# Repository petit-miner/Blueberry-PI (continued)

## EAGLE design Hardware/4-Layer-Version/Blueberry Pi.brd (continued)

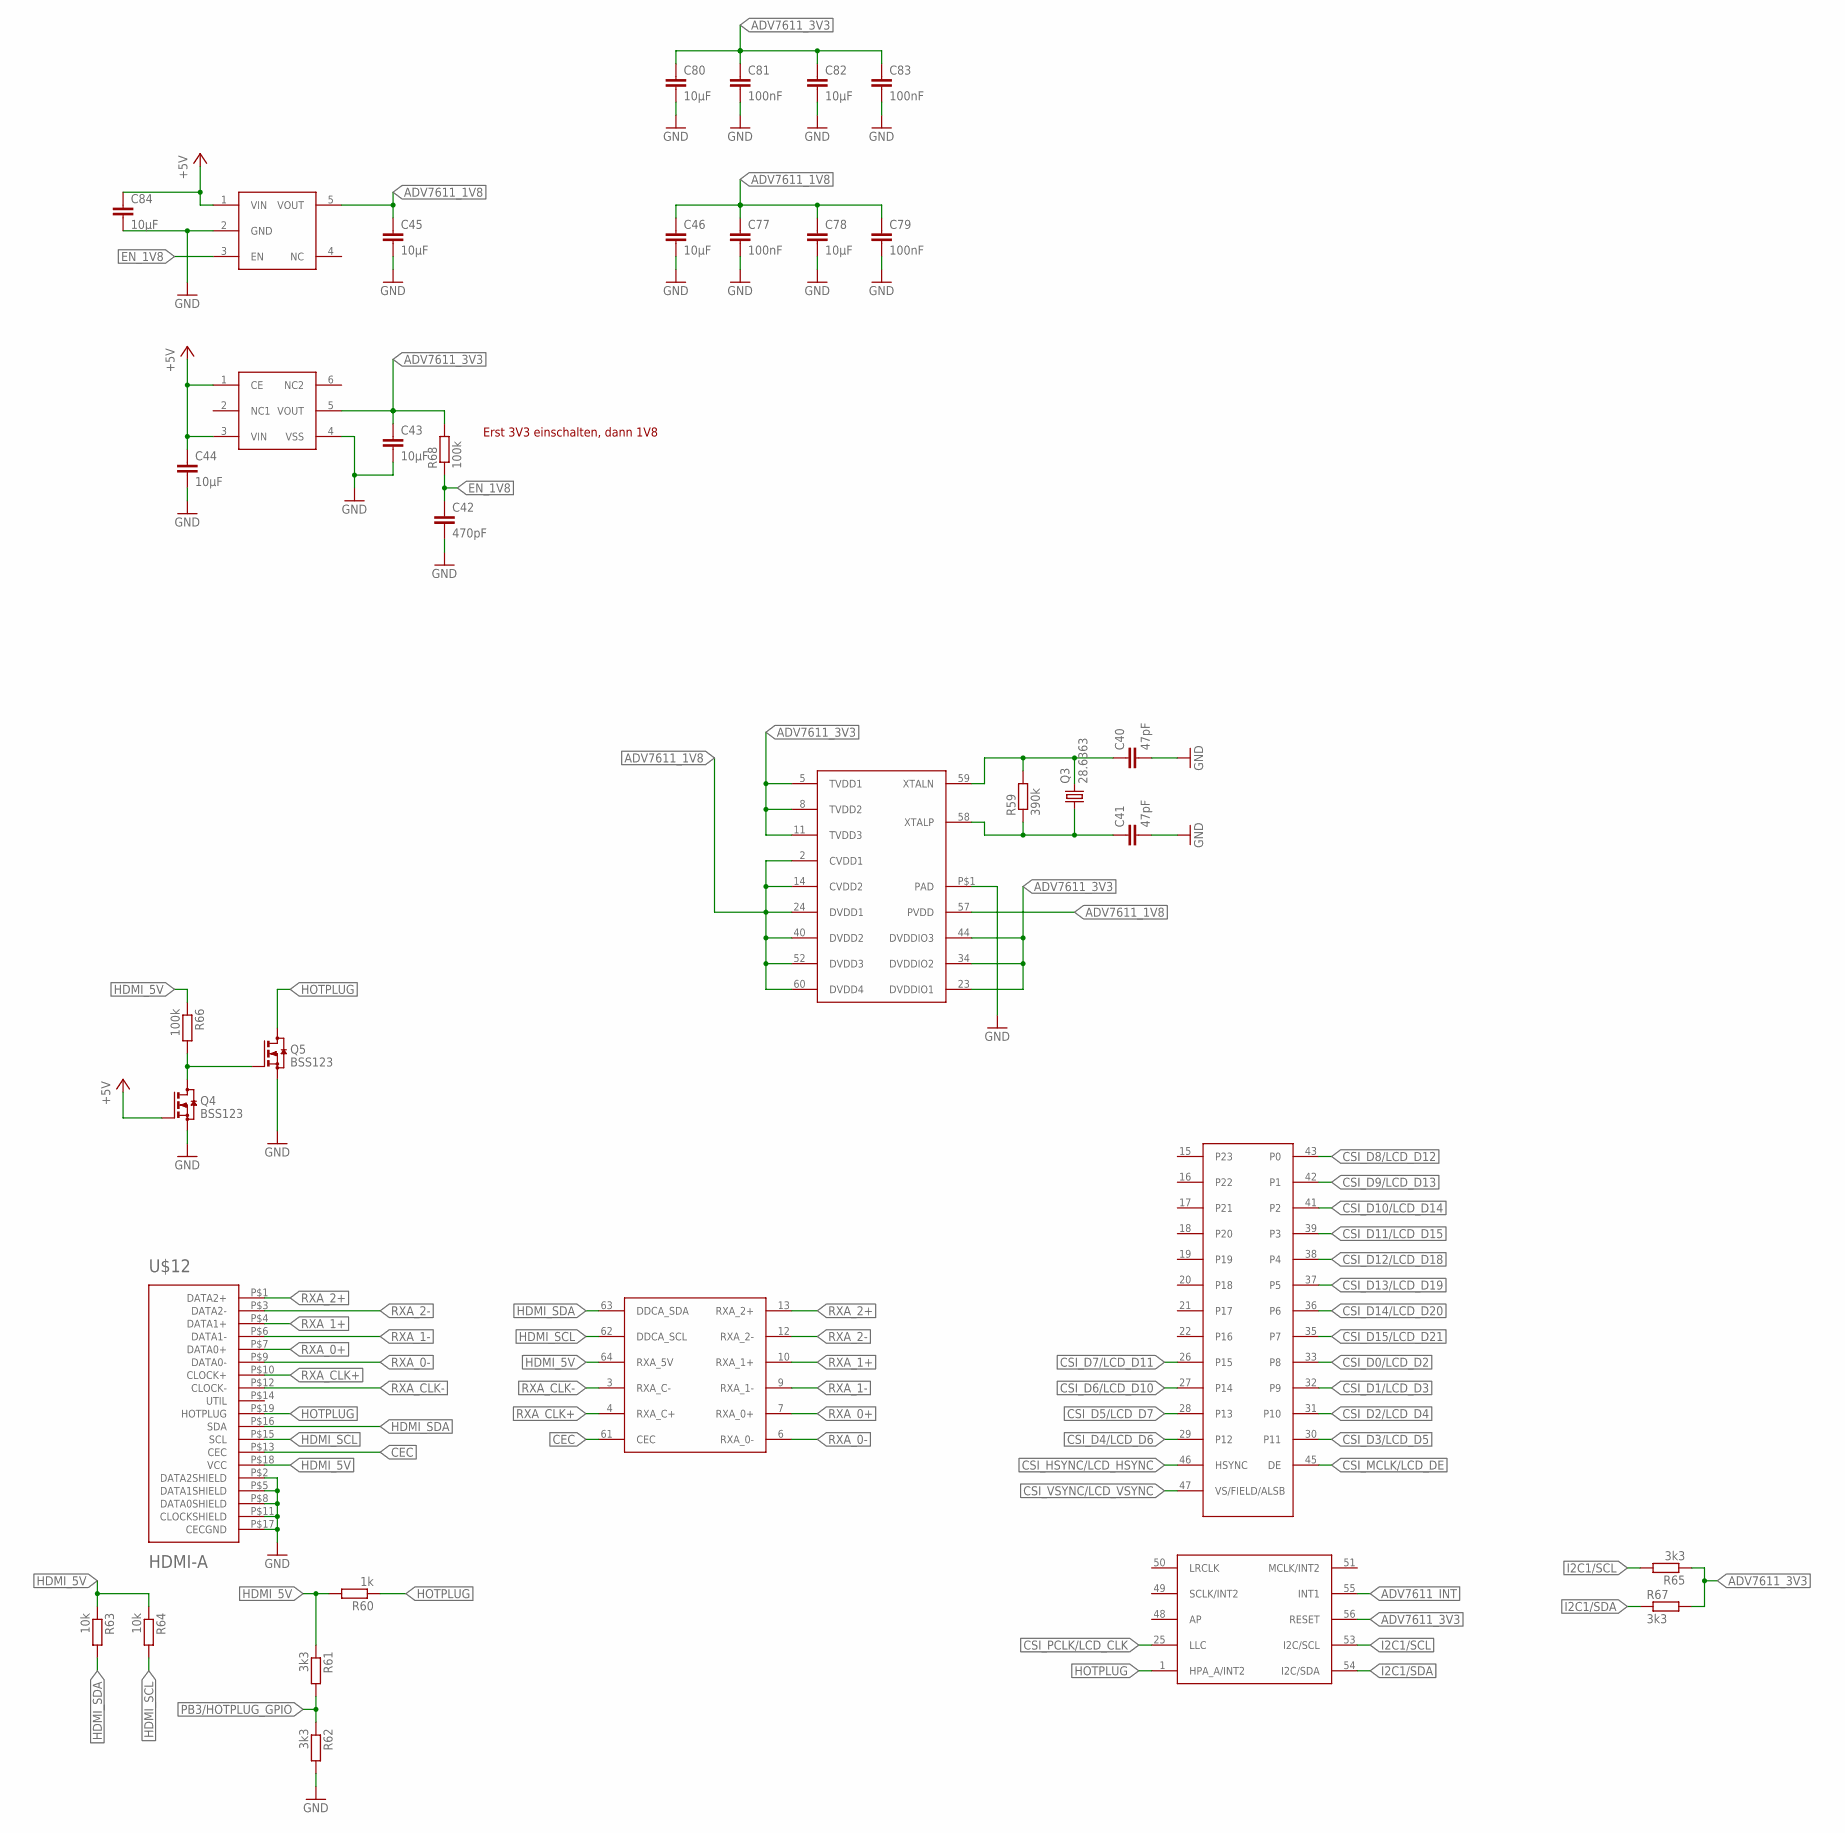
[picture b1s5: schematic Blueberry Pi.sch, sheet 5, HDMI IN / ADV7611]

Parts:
C40, C41: 47pF; C0603
C42: 470pF; C0603
C43, C44, C45, C46, C78, C80, C82, C84: 10µF; C0805
C77, C79, C81, C83: 100nF; C0603
Q3: 28.6363; HC49/S
Q4, Q5: BSS123; SOT23
R59: 390k; R0603
R60: 1k; R0603
R61, R62, R65, R67: 3k3; R0603
R63, R64: 10k; R0603
R66, R68: 100k; R0603
U$5: ADV7611; QFP50P1210X1210X120-65T500
U$12: HDMI-A; HDMI_A
U$13: XC6210B332MR-G; SOT-25
U$14: RT9013-18GB; SOT-23-5

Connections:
+5V: C44.1, C84.1, Q4.1 (G), U$13.1 (CE), U$13.3 (VIN), U$14.1 (VIN); also elsewhere on the board
ADV7611_1V8: C45.1, C46.1, C77.1, C78.1, C79.1, U$5.2 (CVDD1), U$5.14 (CVDD2), U$5.24 (DVDD1), U$5.40 (DVDD2), U$5.52 (DVDD3), U$5.57 (PVDD), U$5.60 (DVDD4), U$14.5 (VOUT)
ADV7611_3V3: C43.1, C80.1, C81.1, C82.1, C83.1, R65.1, R67.2, R68.2, U$5.5 (TVDD1), U$5.8 (TVDD2), U$5.11 (TVDD3), U$5.23 (DVDDIO1), U$5.34 (DVDDIO2), U$5.44 (DVDDIO3), U$5.56 (RESET), U$13.5 (VOUT)
ADV7611_INT: U$5.55 (INT1)
CEC: U$5.61 (CEC), U$12.P$13 (CEC)
CSI_D0/LCD_D2: U$5.33 (P8); also elsewhere on the board
CSI_D1/LCD_D3: U$5.32 (P9); also elsewhere on the board
CSI_D2/LCD_D4: U$5.31 (P10); also elsewhere on the board
CSI_D3/LCD_D5: U$5.30 (P11); also elsewhere on the board
CSI_D4/LCD_D6: U$5.29 (P12); also elsewhere on the board
CSI_D5/LCD_D7: U$5.28 (P13); also elsewhere on the board
CSI_D6/LCD_D10: U$5.27 (P14); also elsewhere on the board
CSI_D7/LCD_D11: U$5.26 (P15); also elsewhere on the board
CSI_D8/LCD_D12: U$5.43 (P0); also elsewhere on the board
CSI_D9/LCD_D13: U$5.42 (P1); also elsewhere on the board
CSI_D10/LCD_D14: U$5.41 (P2); also elsewhere on the board
CSI_D11/LCD_D15: U$5.39 (P3); also elsewhere on the board
CSI_D12/LCD_D18: U$5.38 (P4); also elsewhere on the board
CSI_D13/LCD_D19: U$5.37 (P5); also elsewhere on the board
CSI_D14/LCD_D20: U$5.36 (P6); also elsewhere on the board
CSI_D15/LCD_D21: U$5.35 (P7); also elsewhere on the board
CSI_HSYNC/LCD_HSYNC: U$5.46 (HSYNC); also elsewhere on the board
CSI_MCLK/LCD_DE: U$5.45 (DE); also elsewhere on the board
CSI_PCLK/LCD_CLK: U$5.25 (LLC); also elsewhere on the board
CSI_VSYNC/LCD_VSYNC: U$5.47 (VS/FIELD/ALSB); also elsewhere on the board
EN_1V8: C42.1, R68.1, U$14.3 (EN)
GND: C40.2, C41.2, C42.2, C43.2, C44.2, C45.2, C46.2, C77.2, C78.2, C79.2, C80.2, C81.2, C82.2, C83.2, C84.2, Q4.2 (S), Q5.2 (S), R62.2, U$5.P$1 (PAD), U$12.P$2 (DATA2SHIELD), U$12.P$5 (DATA1SHIELD), U$12.P$8 (DATA0SHIELD), U$12.P$11 (CLOCKSHIELD), U$12.P$17 (CECGND), U$13.4 (VSS), U$14.2 (GND); also elsewhere on the board
HDMI_5V: R60.2, R61.1, R63.1, R64.1, R66.1, U$5.64 (RXA_5V), U$12.P$18 (VCC)
HDMI_SCL: R64.2, U$5.62 (DDCA_SCL), U$12.P$15 (SCL)
HDMI_SDA: R63.2, U$5.63 (DDCA_SDA), U$12.P$16 (SDA)
HOTPLUG: Q5.3 (D), R60.1, U$5.1 (HPA_A/INT2), U$12.P$19 (HOTPLUG)
I2C1/SCL: R65.2, U$5.53 (I2C/SCL); also elsewhere on the board
I2C1/SDA: R67.1, U$5.54 (I2C/SDA); also elsewhere on the board
unnamed: C40.1, Q3.2, R59.2, U$5.59 (XTALN)
unnamed: C41.1, Q3.1, R59.1, U$5.58 (XTALP)
unnamed: Q4.3 (D), Q5.1 (G), R66.2
PB3/HOTPLUG_GPIO: R61.2, R62.1; also elsewhere on the board
RXA_0+: U$5.7 (RXA_0+), U$12.P$7 (DATA0+)
RXA_0-: U$5.6 (RXA_0-), U$12.P$9 (DATA0-)
RXA_1+: U$5.10 (RXA_1+), U$12.P$4 (DATA1+)
RXA_1-: U$5.9 (RXA_1-), U$12.P$6 (DATA1-)
RXA_2+: U$5.13 (RXA_2+), U$12.P$1 (DATA2+)
RXA_2-: U$5.12 (RXA_2-), U$12.P$3 (DATA2-)
RXA_CLK+: U$5.4 (RXA_C+), U$12.P$10 (CLOCK+)
RXA_CLK-: U$5.3 (RXA_C-), U$12.P$12 (CLOCK-)

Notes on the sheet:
Erst 3V3 einschalten, dann 1V8

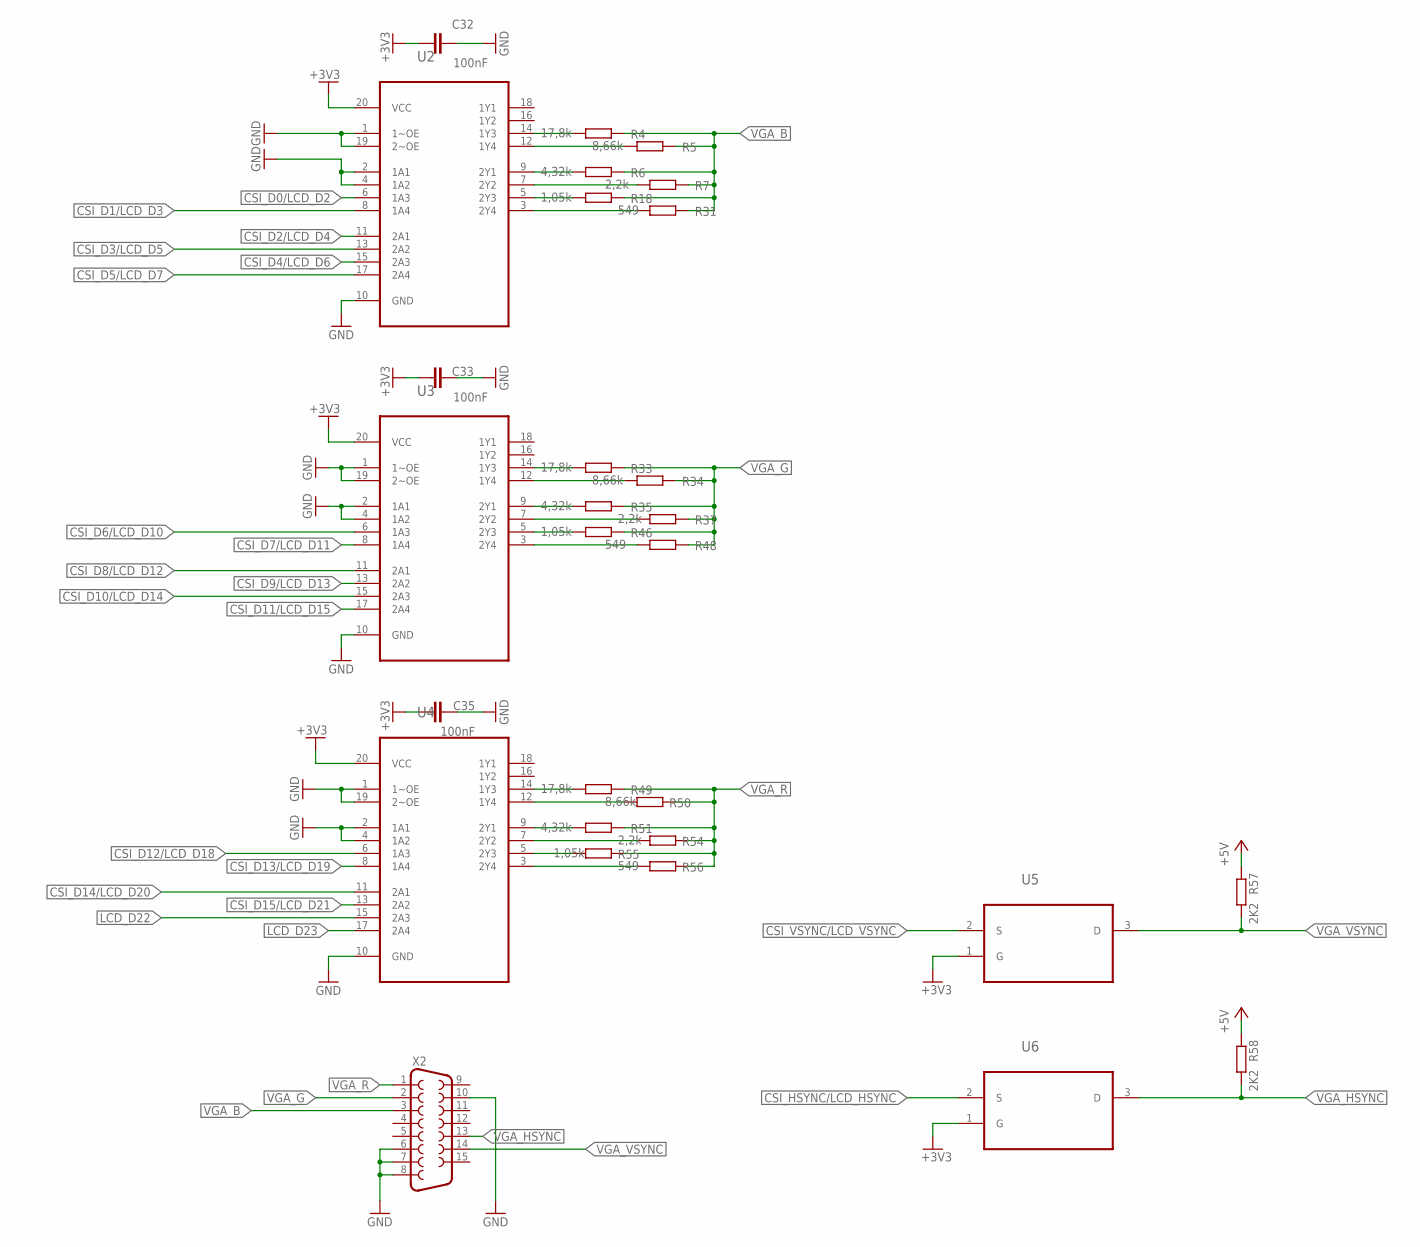
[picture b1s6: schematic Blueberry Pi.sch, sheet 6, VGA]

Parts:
C32, C33, C35: 100nF; C0603
R4, R33, R49: 17,8k; R0603
R5, R34, R50: 8,66k; R0603
R6, R35, R51: 4,32k; R0603
R7, R37, R54: 2,2k; R0603
R18, R46, R55: 1,05k; R0603
R31, R48, R56: 549; R0603
R57, R58: 2K2; R0603
U2, U3, U4: SN74ALVC244PW; SOP65P640X120-20N
U5, U6: BSS138TA; SOT95P240X110-3N
X2: F15HDH; HDF15H

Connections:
+3V3: C32.2, C33.2, C35.2, U2.20 (VCC), U3.20 (VCC), U4.20 (VCC), U5.1 (G), U6.1 (G); also elsewhere on the board
+5V: R57.1, R58.1; also elsewhere on the board
CSI_D0/LCD_D2: U2.6 (1A3); also elsewhere on the board
CSI_D1/LCD_D3: U2.8 (1A4); also elsewhere on the board
CSI_D2/LCD_D4: U2.11 (2A1); also elsewhere on the board
CSI_D3/LCD_D5: U2.13 (2A2); also elsewhere on the board
CSI_D4/LCD_D6: U2.15 (2A3); also elsewhere on the board
CSI_D5/LCD_D7: U2.17 (2A4); also elsewhere on the board
CSI_D6/LCD_D10: U3.6 (1A3); also elsewhere on the board
CSI_D7/LCD_D11: U3.8 (1A4); also elsewhere on the board
CSI_D8/LCD_D12: U3.11 (2A1); also elsewhere on the board
CSI_D9/LCD_D13: U3.13 (2A2); also elsewhere on the board
CSI_D10/LCD_D14: U3.15 (2A3); also elsewhere on the board
CSI_D11/LCD_D15: U3.17 (2A4); also elsewhere on the board
CSI_D12/LCD_D18: U4.6 (1A3); also elsewhere on the board
CSI_D13/LCD_D19: U4.8 (1A4); also elsewhere on the board
CSI_D14/LCD_D20: U4.11 (2A1); also elsewhere on the board
CSI_D15/LCD_D21: U4.13 (2A2); also elsewhere on the board
CSI_HSYNC/LCD_HSYNC: U6.2 (S); also elsewhere on the board
CSI_VSYNC/LCD_VSYNC: U5.2 (S); also elsewhere on the board
GND: C32.1, C33.1, C35.1, U2.1 (1~OE), U2.2 (1A1), U2.4 (1A2), U2.10 (GND), U2.19 (2~OE), U3.1 (1~OE), U3.2 (1A1), U3.4 (1A2), U3.10 (GND), U3.19 (2~OE), U4.1 (1~OE), U4.2 (1A1), U4.4 (1A2), U4.10 (GND), U4.19 (2~OE), X2.6, X2.7, X2.8, X2.10; also elsewhere on the board
LCD_D22: U4.15 (2A3); also elsewhere on the board
LCD_D23: U4.17 (2A4); also elsewhere on the board
unnamed: R4.2, U2.14 (1Y3)
unnamed: R5.2, U2.12 (1Y4)
unnamed: R6.2, U2.9 (2Y1)
unnamed: R7.2, U2.7 (2Y2)
unnamed: R18.2, U2.5 (2Y3)
unnamed: R31.2, U2.3 (2Y4)
unnamed: R33.2, U3.14 (1Y3)
unnamed: R34.2, U3.12 (1Y4)
unnamed: R35.2, U3.9 (2Y1)
unnamed: R37.2, U3.7 (2Y2)
unnamed: R46.2, U3.5 (2Y3)
unnamed: R48.2, U3.3 (2Y4)
unnamed: R56.2, U4.3 (2Y4)
unnamed: R55.2, U4.5 (2Y3)
unnamed: R54.2, U4.7 (2Y2)
unnamed: R51.2, U4.9 (2Y1)
unnamed: R50.2, U4.12 (1Y4)
unnamed: R49.2, U4.14 (1Y3)
VGA_B: R4.1, R5.1, R6.1, R7.1, R18.1, R31.1, X2.3
VGA_G: R33.1, R34.1, R35.1, R37.1, R46.1, R48.1, X2.2
VGA_HSYNC: R58.2, U6.3 (D), X2.13
VGA_R: R49.1, R50.1, R51.1, R54.1, R55.1, R56.1, X2.1
VGA_VSYNC: R57.2, U5.3 (D), X2.14

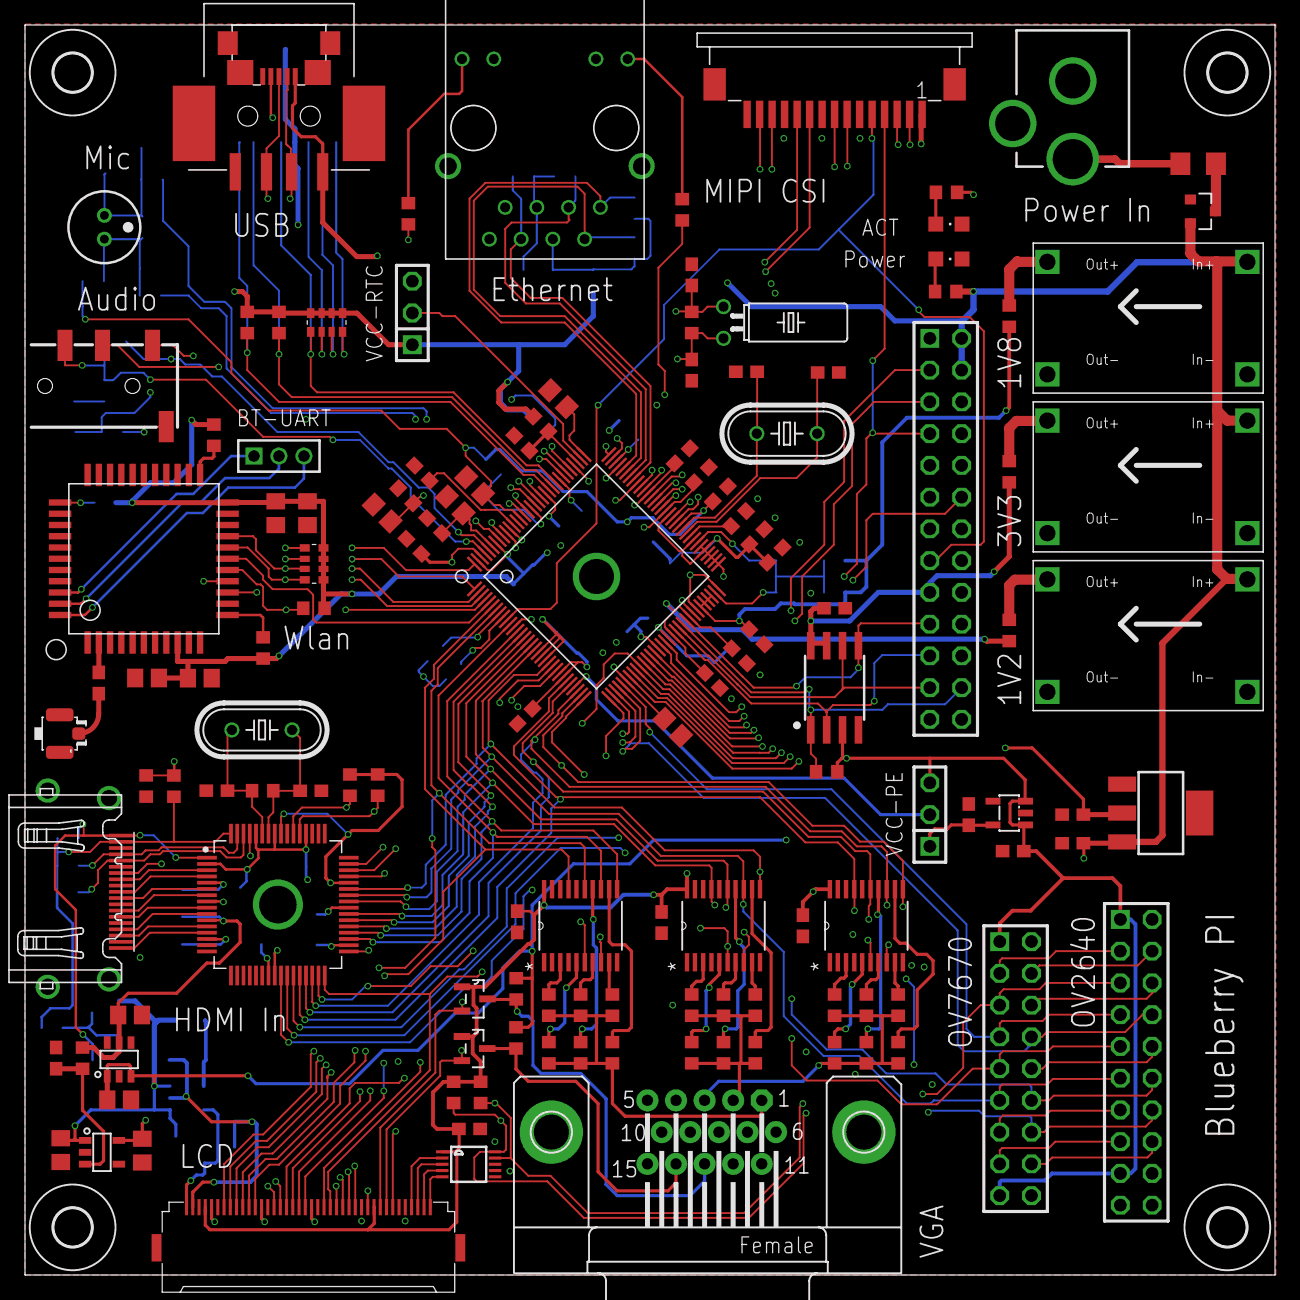
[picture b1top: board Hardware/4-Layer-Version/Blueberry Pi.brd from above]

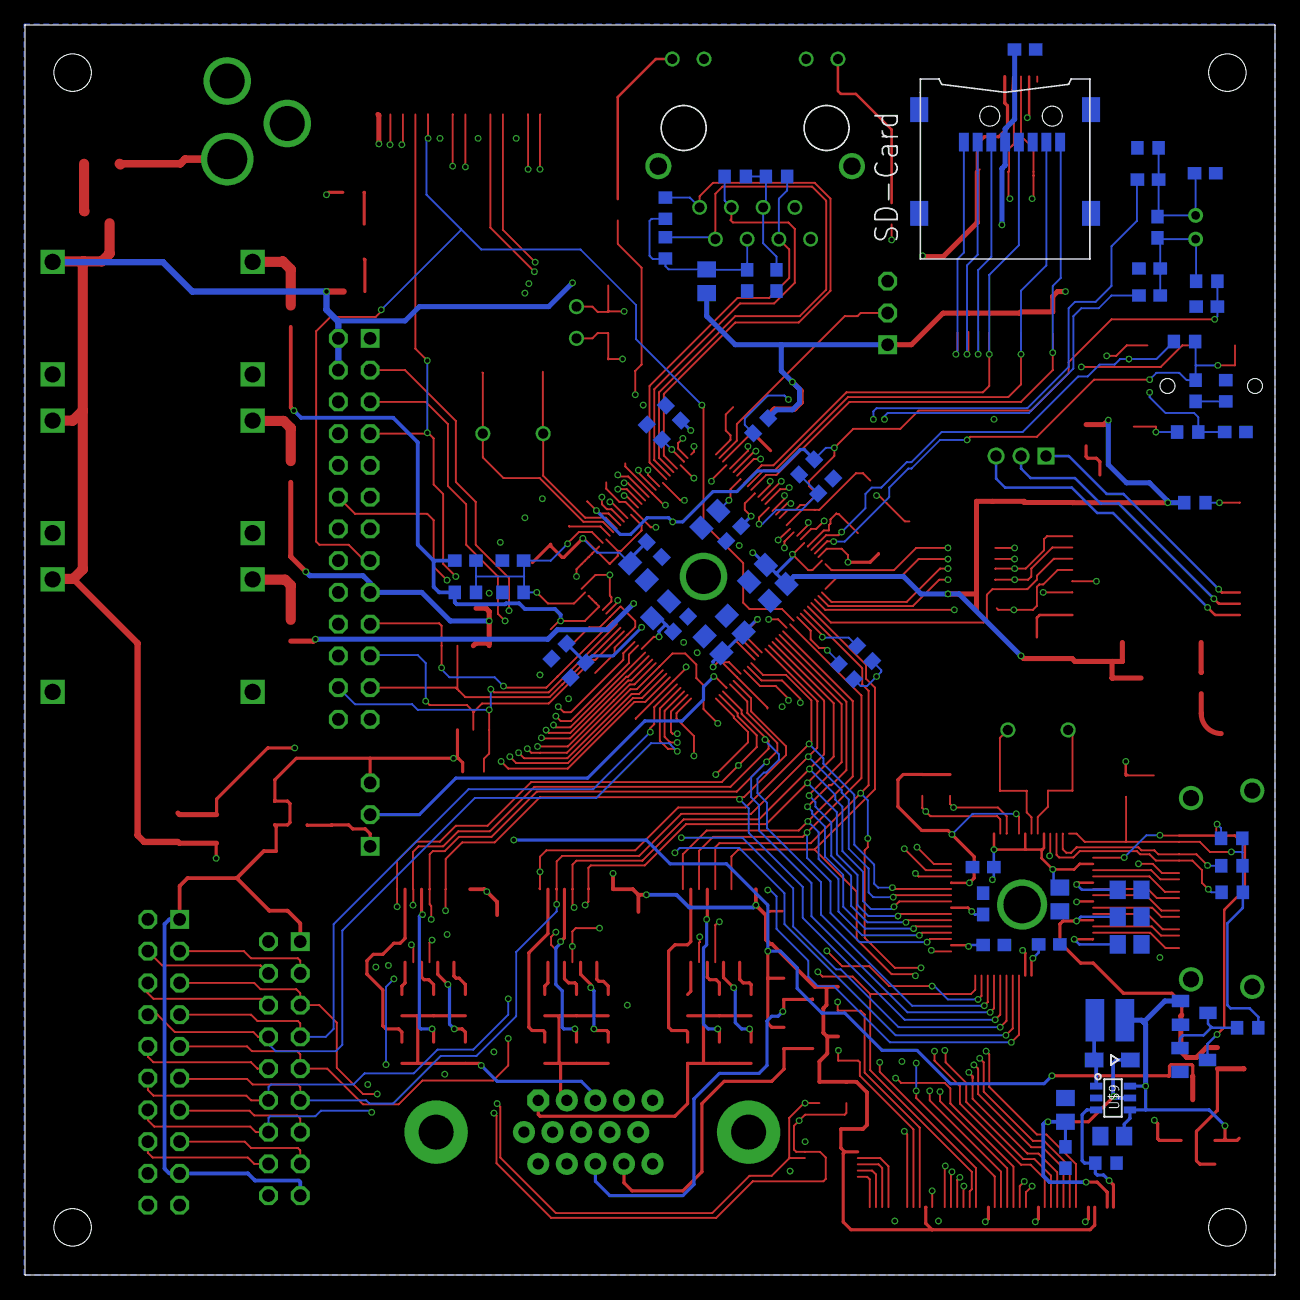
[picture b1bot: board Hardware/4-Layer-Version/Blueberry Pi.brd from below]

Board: 4 copper layers, 100.0 x 100.0 mm, 202 parts (67 on the bottom side), 167 nets.

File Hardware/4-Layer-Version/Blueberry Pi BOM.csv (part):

"Qty";"Value";"Device";"Package";"Parts";"Description";"MF";"MPN";"OC_FARNELL";"OC_NEWARK";"PACKAGE";"PROD_ID";"SF_ID";"SPICEPREFIX";"SUPPLIER";"VALUE";
"1";"";"40PINFPCH15-1LW";"XF2H-4015-1LW";"J3";"OMRON FPC Connector";"";"";"";"";"";"";"";"";"";"";
"2";"";"4R-NEXB38V";"EXB38V";"RN1, RN2";"Array Chip Resistor";"";"";"unknown";"unknown";"";"";"";"";"";"";
"1";"";"68611514122";"68611514122";"J4";"WR-FPC 1.00mm SMT ZIF Horizontal Top Contact, 15 Pins=>Code : Con_FPC_ZIF_1.00_68611514122";"";"";"";"";"";"";"";"";"";"";
"2";"";"BSS138TA";"SOT95P240X110-3N";"U5, U6";"N-CHANNEL ENHANCEMENT MODE MOSFET";"";"BSS138TA";"1471176";"61M5072";"SOT-23-3";"";"";"";"Diodes Inc";"";
"1";"";"CON-HIROSE_MICRO-USB-SHIELD-ZX62R-B-5P";"CON-HIROSE_ZX62R-B-5P";"U$15";"Hirose Micro USB Connector";"";"";"";"";"";"";"";"";"";"";
"1";"";"DCBARRELPTH";"DCJACK_2MM_PTH";"CN2";"2.0mm DC Barrel Jack";"";"";"";"";"";"";"";"";"";"";
"1";"";"DIODE-SOD323-W";"SOD323-W";"D1";"DIODE";"";"";"";"";"";"";"";"";"";"";
"1";"";"ELECTRET_MICROPHON-F6035AP";"F6035AP";"MIC";"Electret Condenser Microphone";"";"";"";"";"";"";"";"";"";"";
"1";"";"F15HDH";"HDF15H";"X2";"SUB-D";"";"";"";"";"";"";"";"";"";"";
"2";"";"LEDCHIPLED_0805";"CHIPLED_0805";"LED1, LED2";"LED";"";"";"";"";"";"";"";"";"";"";
"1";"";"LM1117";"SOT223";"IC1";"";"";"";"";"";"";"";"";"";"";"";
"1";"";"PINHD-1X3";"1X03";"JP3";"PIN HEADER";"";"";"";"";"";"";"";"";"";"";
"1";"";"PINHD-1X3M";"1X03M";"JP7";"PIN HEADER";"";"";"";"";"";"";"";"";"";"";
"1";"";"PINHD-2X13";"2X13";"JP1";"PIN HEADER";"";"";"";"";"";"";"";"";"";"";
"3";"";"SN74ALVC244PW";"SOP65P640X120-20N";"U2, U3, U4";"OCTAL BUFFERS/DRIVERS WITH 3-STATE OUTPUTS";"";"SN74ALVC244PW";"1470750";"36K3549";"TSSOP-20";"";"";"";"Texas Instruments";"";
"1";"0";"R-EU_R0603";"R0603";"R26";"RESISTOR, European symbol";"";"";"";"";"";"";"";"";"";"";
"3";"0R";"R-EU_R0603";"R0603";"R69, R70, R71";"RESISTOR, European symbol";"";"";"";"";"";"";"";"";"";"";
"3";"1,05k";"R-EU_R0603";"R0603";"R18, R46, R55";"RESISTOR, European symbol";"";"";"";"";"";"";"";"";"";"";
"2";"100k";"R-EU_R0603";"R0603";"R9, R10";"RESISTOR, European symbol";"";"";"";"";"";"";"";"";"";"";
"2";"100k";"R-EU_R0603";"R0603";"R66, R68";"RESISTOR, European symbol";"";"";"";"";"";"";"";"R";"";"";
"21";"100nF";"C-EUC0603";"C0603";"C1, C2, C9, C14, C15, C18, C22, C27, C28, C32, C33, C35, C48, C49, C51, C53, C57, C58, C62, C67, C70";"CAPACITOR, European symbol";"";"";"";"";"";"";"";"";"";"";
"4";"100nF";"C-EUC0603";"C0603";"C77, C79, C81, C83";"CAPACITOR, European symbol";"";"";"";"";"";"";"";"C";"";"";
"3";"100nF";"C-EUC0805";"C0805";"C52, C63, C69";"CAPACITOR, European symbol";"";"";"";"";"";"";"";"";"";"";
"5";"100nf";"C-EUC0603";"C0603";"C31, C36, C37, C75, C76";"CAPACITOR, European symbol";"";"";"";"";"";"";"";"";"";"";
"1";"100pF";"C-EUC0603";"C0603";"C25";"CAPACITOR, European symbol";"";"";"";"";"";"";"";"";"";"";
"1";"10M";"R-EU_R0603";"R0603";"R3";"RESISTOR, European symbol";"";"";"";"";"";"";"";"";"";"";
"6";"10k";"R-EU_R0603";"R0603";"R8, R19, R38, R39, R44, R45";"RESISTOR, European symbol";"";"";"";"";"";"";"";"";"";"";
"2";"10k";"R-EU_R0603";"R0603";"R63, R64";"RESISTOR, European symbol";"";"";"";"";"";"";"";"R";"";"";
"4";"10µF";"C-EUC0603";"C0603";"C38, C56, C60, C71";"CAPACITOR, European symbol";"";"";"";"";"";"";"";"";"";"";
"13";"10µF";"C-EUC0805";"C0805";"C3, C5, C6, C7, C16, C20, C29, C30, C50, C59, C66, C73, C74";"CAPACITOR, European symbol";"";"";"";"";"";"";"";"";"";"";
"8";"10µF";"C-EUC0805";"C0805";"C43, C44, C45, C46, C78, C80, C82, C84";"CAPACITOR, European symbol";"";"";"";"";"";"";"";"C";"";"";
"1";"10µH";"L-EUL0805";"L0805";"L2";"INDUCTOR, European symbol";"";"";"";"";"";"";"";"";"";"";
"3";"17,8k";"R-EU_R0603";"R0603";"R4, R33, R49";"RESISTOR, European symbol";"";"";"";"";"";"";"";"";"";"";
"4";"18pF";"C-EUC0603";"C0603";"C8, C10, C11, C12";"CAPACITOR, European symbol";"";"";"";"";"";"";"";"";"";"";
"4";"1k";"R-EU_R0603";"R0603";"R16, R17, R52, R53";"RESISTOR, European symbol";"";"";"";"";"";"";"";"";"";"";
"1";"1k";"R-EU_R0603";"R0603";"R60";"RESISTOR, European symbol";"";"";"";"";"";"";"";"R";"";"";
"1";"1nF";"C-EUC0603";"C0603";"C34";"CAPACITOR, European symbol";"";"";"";"";"";"";"";"";"";"";
"8";"1µF";"C-EUC0603";"C0603";"C13, C17, C21, C39, C47, C55, C64, C65";"CAPACITOR, European symbol";"";"";"";"";"";"";"";"";"";"";
"2";"1µF";"C-EUC0805";"C0805";"C54, C61";"CAPACITOR, European symbol";"";"";"";"";"";"";"";"";"";"";
"3";"2,2k";"R-EU_R0603";"R0603";"R7, R37, R54";"RESISTOR, European symbol";"";"";"";"";"";"";"";"";"";"";
"1";"2,2µH";"L-EU";"ODD-INDUCTOR";"L1";"INDUCTOR, European symbol";"";"";"";"";"";"";"";"";"";"";
"1";"200k 1%";"R-EU_R0603";"R0603";"R27";"RESISTOR, European symbol";"";"";"";"";"";"";"";"";"";"";
"1";"22";"R-EU_R0603";"R0603";"R15";"RESISTOR, European symbol";"";"";"";"";"";"";"";"";"";"";
"1";"240 - 1%";"R-EU_R0603";"R0603";"R12";"RESISTOR, European symbol";"";"";"";"";"";"";"";"";"";"";
"1";"24Mhz";"CRYSTALHC49U-V";"HC49U-V";"Q1";"CRYSTAL";"";"";"1666969";"unknown";"";"";"";"";"";"";
"1";"25F32006WSOI";"SPI_FLASH-X25XXSMD1";"SO08-EIAJ";"U1";"32M Serial Flash Memory";"";"";"";"";"";"IC-09109";"";"";"";"25F32006WSOI";
"1";"28.6363";"CRYSTALHC49S";"HC49/S";"Q3";"CRYSTAL";"";"";"1667008";"unknown";"";"";"";"";"";"";
"1";"2A";"PTCFUSE-1206";"R1206";"F1";"PTC fuses, resettable thermistors";"";"";"";"";"";"";"";"";"";"";
"2";"2K2";"R-EU_R0603";"R0603";"R57, R58";"RESISTOR, European symbol";"";"";"";"";"";"";"";"";"";"";
"3";"2k";"R-EU_R0603";"R0603";"R25, R28, R30";"RESISTOR, European symbol";"";"";"";"";"";"";"";"";"";"";
"2";"2k - 1%";"R-EU_R0603";"R0603";"R13, R14";"RESISTOR, European symbol";"";"";"";"";"";"";"";"";"";"";
"1";"32kHz";"CRYSTALTC38H";"TC38H";"Q2";"CRYSTAL";"";"";"unknown";"unknown";"";"";"";"";"";"";
"4";"33pF";"C-EUC0603";"C0603";"C4, C23, C24, C26";"CAPACITOR, European symbol";"";"";"";"";"";"";"";"";"";"";
"1";"390k";"R-EU_R0603";"R0603";"R59";"RESISTOR, European symbol";"";"";"";"";"";"";"";"R";"";"";
"4";"3k3";"R-EU_R0603";"R0603";"R61, R62, R65, R67";"RESISTOR, European symbol";"";"";"";"";"";"";"";"R";"";"";
"3";"4,32k";"R-EU_R0603";"R0603";"R6, R35, R51";"RESISTOR, European symbol";"";"";"";"";"";"";"";"";"";"";
"1";"470pF";"C-EUC0603";"C0603";"C42";"CAPACITOR, European symbol";"";"";"";"";"";"";"";"C";"";"";
"6";"47k";"R-EU_R0603";"R0603";"R1, R2, R11, R29, R32, R36";"RESISTOR, European symbol";"";"";"";"";"";"";"";"";"";"";
"2";"47pF";"C-EUC0603";"C0603";"C40, C41";"CAPACITOR, European symbol";"";"";"";"";"";"";"";"C";"";"";
"4";"49.9";"R-EU_R0603";"R0603";"R40, R41, R42, R43";"RESISTOR, European symbol";"";"";"";"";"";"";"";"";"";"";
"1";"5,1";"R-EU_R0603";"R0603";"R47";"RESISTOR, European symbol";"";"";"";"";"";"";"";"";"";"";
"3";"549";"R-EU_R0603";"R0603";"R31, R48, R56";"RESISTOR, European symbol";"";"";"";"";"";"";"";"";"";"";
"1";"6k 1%";"R-EU_R0603";"R0603";"R24";"RESISTOR, European symbol";"";"";"";"";"";"";"";"";"";"";
"3";"8,66k";"R-EU_R0603";"R0603";"R5, R34, R50";"RESISTOR, European symbol";"";"";"";"";"";"";"";"";"";"";
"1";"ADV7611";"ADV7611";"QFP50P1210X1210X120-65T500";"U$5";"";"";"";"";"";"";"";"";"";"";"";
"1";"AP2305BGN";"P-CHANNEL-MOSFET";"SOT23-3";"U$7";"P-Channel MOSFET Mode Field Effect Transistor";"";"";"";"";"";"";"";"";"";"";
"1";"AUDIO_JACK_SMD";"AUDIO_JACK_TRRSSMD_RA";"AUDIO_JACK_3.5MM_TRRS_SMD_RA";"J2";"Audio Jack - 3.5mm TRRS (SMD)";"";"";"";"";"";"CONN-10676";"PRT-12639";"";"";"";
"2";"BSS123";"BSS123";"SOT23";"Q4, Q5";"N-CHANNEL MOS FET";"";"";"";"";"";"";"";"";"";"";
"1";"HDMI-A";"HDMI-A";"HDMI_A";"U$12";"Horizonal HDMI type "A" jack";"";"";"";"";"";"";"";"";"";"";
"1";"HR911105A";"HR911105A";"RJ45";"U$3";"";"";"";"";"";"";"";"";"";"";"";
"4";"MOUNT-HOLE3.0";"MOUNT-HOLE3.0";"3,0";"H1, H2, H3, H4";"MOUNTING HOLE with drill center marker";"";"";"";"";"";"";"";"";"";"";
"3";"MP1584-MINI";"MP1584-MINI";"MINI-DC-BRICK";"U$4, U$10, U$11";"";"";"";"";"";"";"";"";"";"";"";
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
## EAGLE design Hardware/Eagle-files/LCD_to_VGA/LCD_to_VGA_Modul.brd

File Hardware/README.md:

Hardware

I have ordered the first batch of prototype PCBs, so keep in mind that I haven't tested the PCBs yet. 
If they are tested I will change these readme.

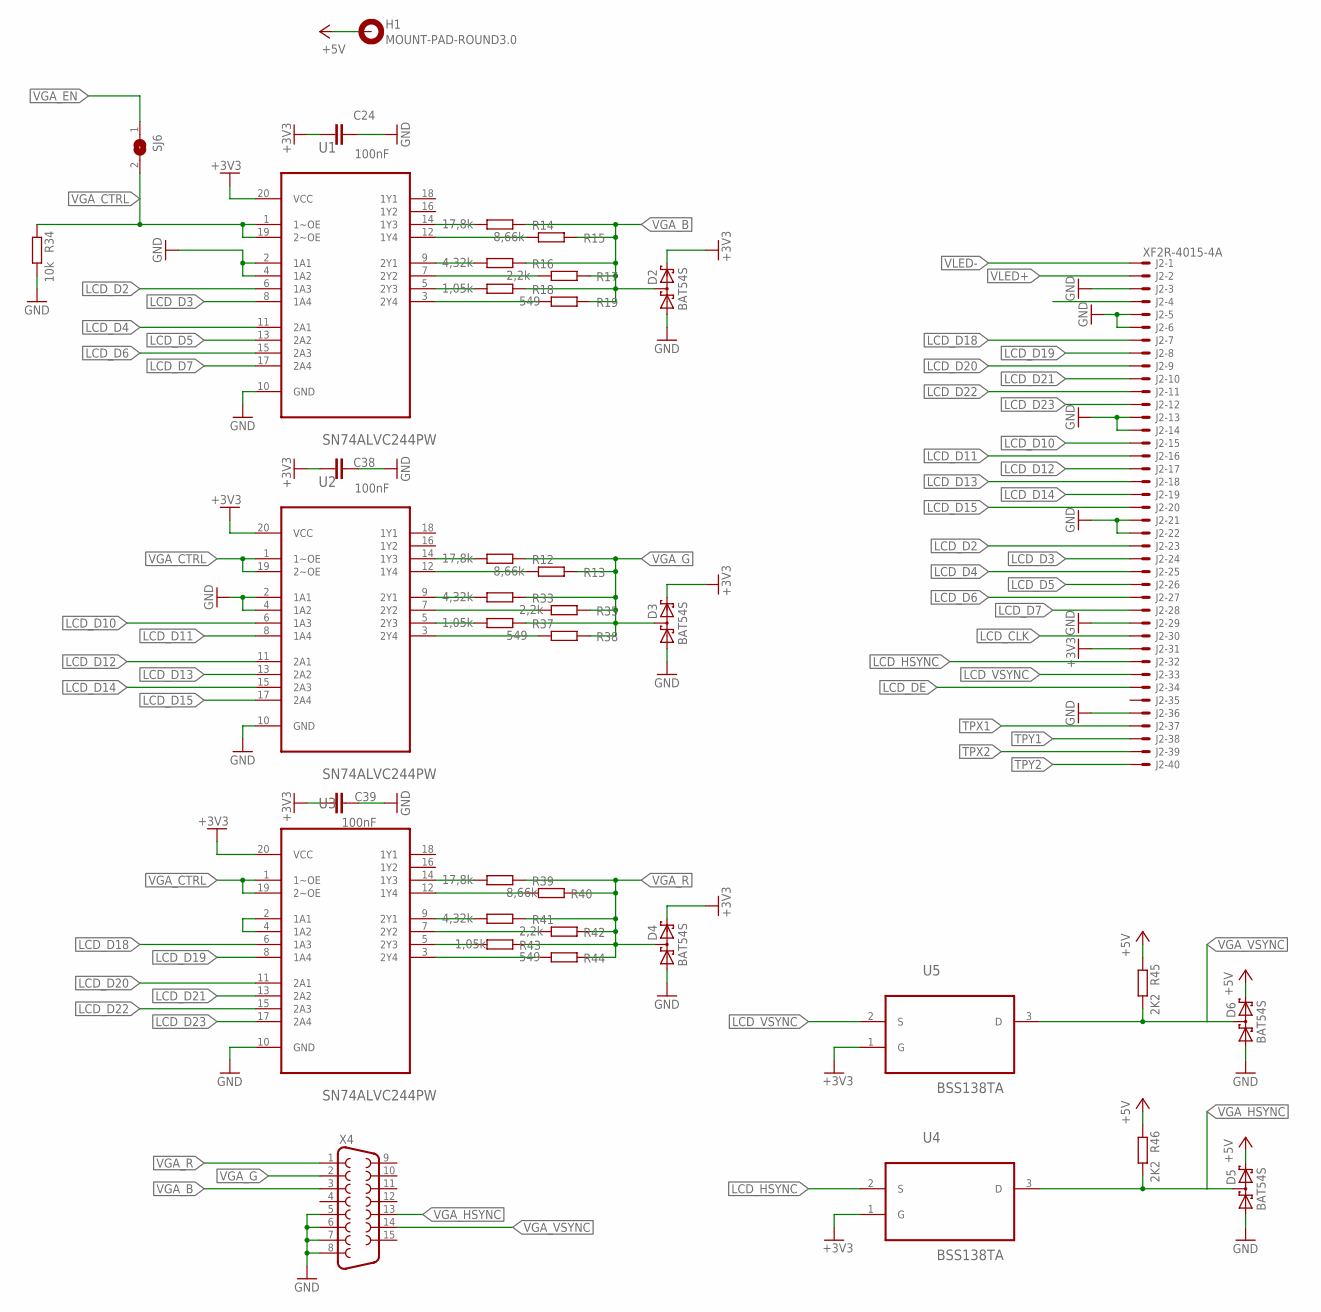
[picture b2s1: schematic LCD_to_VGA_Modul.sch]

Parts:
C24, C38, C39: 100nF; C0805
D2, D3, D4, D5, D6: BAT54S; SOT23
H1: MOUNT-PAD-ROUND3.0; 3,0-PAD
J2: XF2R-4015-4A
R12, R14, R39: 17,8k; R0805
R13, R15, R40: 8,66k; R0805
R16, R33, R41: 4,32k; R0805
R17, R35, R42: 2,2k; R0805
R18, R37, R43: 1,05k; R0805
R19, R38, R44: 549; R0805
R34: 10k; R0805
R45, R46: 2K2; R0805
SJ6: SJ
U1, U2, U3: SN74ALVC244PW; SOP65P640X120-20N
U4, U5: BSS138TA; SOT95P240X110-3N
X4: F15H

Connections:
+3V3: C24.2, C38.2, C39.2, D2.2 (K2), D3.2 (K2), D4.2 (K2), J2.31 (MS), U1.20 (VCC), U2.20 (VCC), U3.20 (VCC), U4.1 (G), U5.1 (G)
+5V: D5.2 (K2), D6.2 (K2), H1.B3,0, R45.1, R46.1
GND: C24.1, C38.1, C39.1, D2.1 (A1), D3.1 (A1), D4.1 (A1), D5.1 (A1), D6.1 (A1), J2.3 (MS), J2.5 (MS), J2.6 (MS), J2.13 (MS), J2.14 (MS), J2.21 (MS), J2.22 (MS), J2.29 (MS), J2.36 (MS), R34.2, U1.2 (1A1), U1.4 (1A2), U1.10 (GND), U2.2 (1A1), U2.4 (1A2), U2.10 (GND), U3.10 (GND), X4.5, X4.6, X4.7, X4.8
LCD_CLK: J2.30 (MS)
LCD_D2: J2.23 (MS), U1.6 (1A3)
LCD_D3: J2.24 (MS), U1.8 (1A4)
LCD_D4: J2.25 (MS), U1.11 (2A1)
LCD_D5: J2.26 (MS), U1.13 (2A2)
LCD_D6: J2.27 (MS), U1.15 (2A3)
LCD_D7: J2.28 (MS), U1.17 (2A4)
LCD_D10: J2.15 (MS), U2.6 (1A3)
LCD_D11: J2.16 (MS), U2.8 (1A4)
LCD_D12: J2.17 (MS), U2.11 (2A1)
LCD_D13: J2.18 (MS), U2.13 (2A2)
LCD_D14: J2.19 (MS), U2.15 (2A3)
LCD_D15: J2.20 (MS), U2.17 (2A4)
LCD_D18: J2.7 (MS), U3.6 (1A3)
LCD_D19: J2.8 (MS), U3.8 (1A4)
LCD_D20: J2.9 (MS), U3.11 (2A1)
LCD_D21: J2.10 (MS), U3.13 (2A2)
LCD_D22: J2.11 (MS), U3.15 (2A3)
LCD_D23: J2.12 (MS), U3.17 (2A4)
LCD_DE: J2.34 (MS)
LCD_HSYNC: J2.32 (MS), U4.2 (S)
LCD_VSYNC: J2.33 (MS), U5.2 (S)
unnamed: R12.2, U2.14 (1Y3)
unnamed: R13.2, U2.12 (1Y4)
unnamed: R14.2, U1.14 (1Y3)
unnamed: R15.2, U1.12 (1Y4)
unnamed: R16.2, U1.9 (2Y1)
unnamed: R17.2, U1.7 (2Y2)
unnamed: R18.2, U1.5 (2Y3)
unnamed: R19.2, U1.3 (2Y4)
unnamed: U3.2 (1A1), U3.4 (1A2)
unnamed: R33.2, U2.9 (2Y1)
unnamed: R35.2, U2.7 (2Y2)
unnamed: R37.2, U2.5 (2Y3)
unnamed: R38.2, U2.3 (2Y4)
unnamed: R44.2, U3.3 (2Y4)
unnamed: R43.2, U3.5 (2Y3)
unnamed: R42.2, U3.7 (2Y2)
unnamed: R41.2, U3.9 (2Y1)
unnamed: R40.2, U3.12 (1Y4)
unnamed: R39.2, U3.14 (1Y3)
TPX1: J2.37 (MS)
TPX2: J2.39 (MS)
TPY1: J2.38 (MS)
TPY2: J2.40 (MS)
VGA_B: D2.3 (K1A2), R14.1, R15.1, R16.1, R17.1, R18.1, R19.1, X4.3
VGA_CTRL: R34.1, SJ6.2, U1.1 (1~OE), U1.19 (2~OE), U2.1 (1~OE), U2.19 (2~OE), U3.1 (1~OE), U3.19 (2~OE)
VGA_EN: SJ6.1
VGA_G: D3.3 (K1A2), R12.1, R13.1, R33.1, R35.1, R37.1, R38.1, X4.2
VGA_HSYNC: D5.3 (K1A2), R46.2, U4.3 (D), X4.13
VGA_R: D4.3 (K1A2), R39.1, R40.1, R41.1, R42.1, R43.1, R44.1, X4.1
VGA_VSYNC: D6.3 (K1A2), R45.2, U5.3 (D), X4.14
VLED+: J2.2 (MS)
VLED-: J2.1 (MSV)

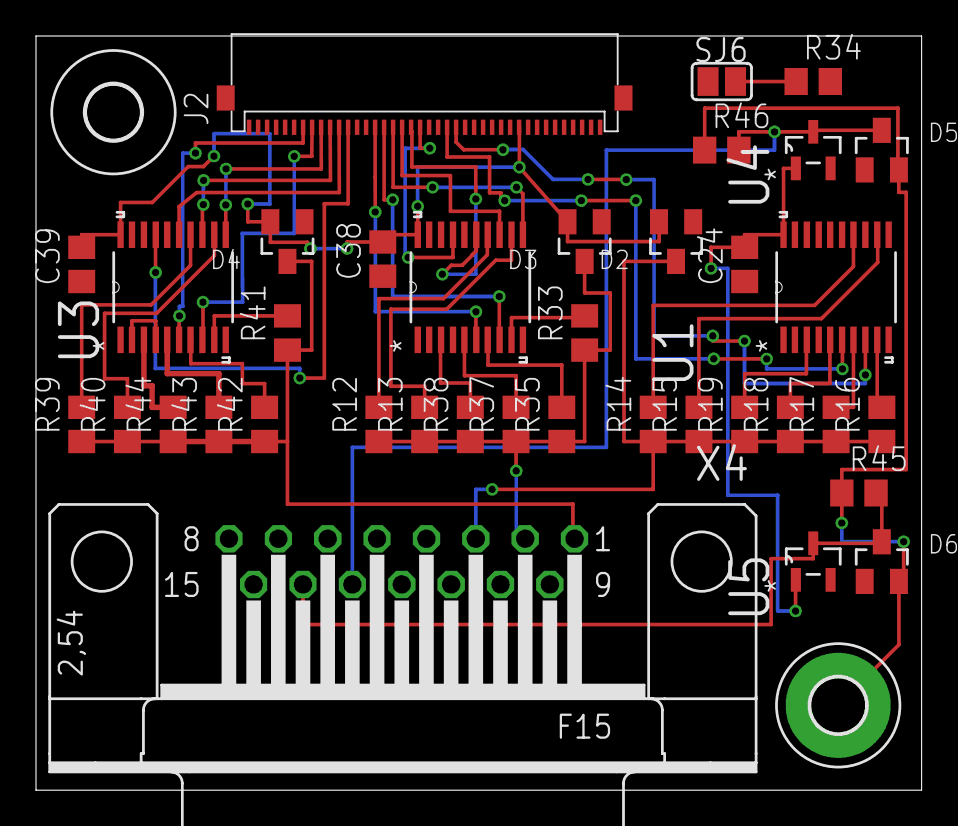
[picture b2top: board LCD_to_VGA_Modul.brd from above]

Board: 2 copper layers, 49.2 x 41.9 mm, 39 parts (0 on the bottom side), 48 nets.

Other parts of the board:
U$3: 3,0
